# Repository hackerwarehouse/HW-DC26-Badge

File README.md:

# HW-DC26-Badge
This is the project page for the Hacker Warehouse electronic badge that was made for DEF CON 26.

## Badge Hardware Specs
* ESP32
* Atmel 32u4
* 96×64 Graphic Full Color OLED Display
* 14x Mini NeoPixel RGB LEDs
* 4 tactile buttons
* 8 Mb Storage
* 2x2 "[Shitty Add-on](https://hackaday.io/project/52950-defcon-26-shitty-add-ons "Shitty Add-on")" support
* Powered via 2 AA batteries or USB

## Badge Functions
* HID Arsenal
	* Ducky script compatible payloads (Windows and Linux demo payloads included)
	* Expanded ducky commands to support mouse movement and clicks
	* Static strings (yubico like)
	* Mouse jiggler (anti screensaver)
	* Time-based One-Time Password and HMAC-based One-Time Password (Google Authenticator mode /w keyboard insertion on demand)
* WiFi Tools
	* 802.11 channel activity monitor
	* Access point scanner / Open AP detector
	* Packet Monitor and Deauth sniffer
	* Can act as a client or access point
	* Webserver (edit filesystem files, trigger payloads remotely)
	* NTP client
* LED patterns and OLED graphics
* Misc. extras

## Usage Instructions
### Power Switch
In order to turn on the device, it must be powered via 2 AA batteries or USB. The main power switch is between the eyes.

### Buttons / UI

Up and Down is on the left side of the OLED, and Left and Right is on the right side of the OLED. From left most to right:  Down / Up / Left / Right

In order to go into a menu or run a program, click the right button. To exit most applications, click the left button. Some programs like the snake game require all 4 buttons so there is no way to clean exit, a power cycle is needed. 

### Keyboard and Mouse Payloads
When the badge is connected to a computer through the USB port, it can act as a HID device. The most common uses of that device class is keyboards and mice. Through use of the Ducky language and expanding on it to support mouse movement, the badge can trigger these scripts on demand. 

#### Via Hardware Menu
Navigate to the HID Arsenal menu, then select either the Windows or Linux Payloads menu option, depending on your target device. In the next submenu, there are five slots for payloads and pressing the right button triggers them. The slots are configurable via win.json and lin.json which defines the payload name and file location.

#### Via Webserver
Assuming the Webserver is running (via Server Tools -> Webserver Start), navigate to 10.0.5.1. Authenticate via the credentials on the OLED. You can remotely trigger the stored payloads or write on demand payloads via this interface. The stored payloads read the same win.json and lin.json files. 

### Static Strings
This mode is something like the yubico device. It is simply a static string that you can utilize with another password. This is a method of two factor authentication as the static string would be likely long and complex. Disclaimer: There is no security mechanism in place if someone were to obtain the hardware and this isn't a FIPS certified device.

### Mouse Jiggler
This mode is utilized if you have a device that you don't want the screen saver to be triggered. The mouse will move every few seconds in a defined pattern. This is useful if you have a device that forces a screensaver or device lock after x idle time. 

### Google Authenticator
This mode requires the badge to be connected to an access point that has internet connectivity so it can reach a time server as there is no RTC on the device itself. In the WiFi client tools menu, connect to an AP and make sure NTP is running. From there, in the HID Arsenal menu select the 'Google Auth (TOTP)' submenu. The six digit time based unique code will refresh every seconds. Press the right button to insert that set of digits automatically assuming the badge is connected through USB. 

### Webserver
Navigate to WiFi Server Tools -> Webserver Start. You can access the webserver if running an AP or if connected. The pages are protected through basic authentication, username and password generated dynamically and is provided on the screen.

### Blinky
There are 40+ LED patterns included. We've included our favorites set in a 5 second rotation. You can also trigger each type of pattern individually. 

### Other Modes
There are no hidden modes, but there are a few areas we didn't cover in this set of docs. Explore. 

## Configuration / Customization
### Settings menu in OLED UI
After feedback from last year on brightness settings, there are individual settings for OLED and LED brightness. Region setting is related to WiFi channel scanning.

### JSON configuration files
There are 4 different json files in SPIFFS. There are a couple ways to edit these files and get them loaded on the badge, but the easiest is through the webserver.
1. config.json = Main device configuration. Includes parameters such as LED and OLED brightness settings, ssid/password if connecting to a wireless client network, region information, and google auth HMAC. 
2. lin.json / win.json = Configuration files for the Linux and Windows KB/M payloads. 
3. static.json = Configuration file for the stored static strings. 

### Google Authenticator
If you do not have a 2 factor code from Google already, follow these steps to set obtain one and change your security settings: 
https://myaccount.google.com/security -> Signing into Google -> 2 Factor Authentication -> Authenticator App -> iphone -> click the 'Can't scan it' button and you will get a string of text that looks like this (and remember that your code will be different than this example):

Take that text, remove all the spaces, change the letter casing to all upper case, then 
input the text into config.json

## Compiling Instructions
These instructions will get you a copy of the project up and running on your local machine.
### Prerequisites
What things you need to install the software and how to install them
```
1. Arduino / compiler
2. SparkFun Pro Micro v3 com driver
https://learn.sparkfun.com/tutorials/pro-micro--fio-v3-hookup-guide/installing-windows
https://learn.sparkfun.com/tutorials/pro-micro--fio-v3-hookup-guide/installing-mac--linux
3. Libraries
  https://raw.githubusercontent.com/sparkfun/Arduino_Boards/master/IDE_Board_Manager/package_sparkfun_index.json
  https://github.com/adafruit/Adafruit_NeoPixel
  https://github.com/adafruit/Adafruit-GFX-Library
  https://github.com/adafruit/Adafruit_CircuitPlayground
  https://github.com/kitesurfer1404/WS2812FX
  https://github.com/me-no-dev/ESPAsyncWebServer
  https://github.com/me-no-dev/AsyncTCP
  https://github.com/bblanchon/ArduinoJson
  https://github.com/me-no-dev/arduino-esp32fs-plugin
  Manually copy the SSD_13XX and qMenuSystem folders to Arduino libraries folder. We included a snapshot of the other libraries used in case newer versions break our code.
4. 3.3v FTDI serial cable
5. and of course a Hacker Warehouse DC26 Badge
```
### Compiling / Flashing Atmel Code
* Set the board to SparkFun Pro Micro
* Set the processor as ATmega32u4 3.3v and NOT the 5v one

### Compiling / Flashing ESP Code
* Set the board to SparkFun ESP32 Thing

#### Programming through FTDI port
1. Flash the atmel with the 'atmel-esp32ftdi-pin7' code first, as this toggle pin 7 and the rx/tx switch to change the serial port communiction to the FTDI port
2. Connect FTDI cable to the board while holding the left button down (which is on the right side, top button)
3. Upload code. Speed setting doesn't really matter, we've been using 921600.
4. To put the atmel back to its original state, program 'atmel-km-relay' the code to it.

#### Programming through USB port / Atmel
Pass through programming doesn't work at the time of writing. Communication is passed through, but something is holding up the ESP32 from fully going into the programming mode

### Uploading SPIFFS files
The keyboard/mouse payloads, configuration files, webserver files are all files that are loaded into a special section in storage marked as SPIFFS. While still having pin 7 set to allow for the FTDI connection, use the 'ESP32 Sketch Data Upload' function in the tools menu. This will compress and compile all the files in the 'data' folder, and upload it. 

## Expanding on your own
### Adding to menu
* See files HW-DC26-Badge.ino and mainmenu.h
* Look at the main switch statement in the .ino file
* Look any of the mainmenu.h examples for how it corresponds to the display

### Button mapping / Escape code
* See files HW-DC26-Badge.ino and blinky.cpp 
* Button mapping is in the beginning of the .ino file
* Look at the LED_Flashlight function for an example of button usage and how to quit the loop and go back to main menu

## Background / timeline of badge development
* Second custom hardware / electronics project trying to improve upon the things we learned from last year
	* Changed from the ESP8266 to the newer ESP32 so we could leverage prior code and focus on enhancements 
	* Added an LDO regulator so badge or connected computer doesn't freak out on voltage
* 3 hardware revisions = 2 prototype runs = 4-5 months
	* The hardware revisions this year were minor in comparison to last year. It was mainly due to the 2x2 Shitty Add-on and orientation of the connector
	* Tried to start earlier (lesson learned last year) but scheduling conflicts put us back to essentially the same timeline as last year
* 5 week code sprint before code needing to be frozen for mass badge flashing
	* This was a massive improvement from last year from a time / rush perspective
	* Still wanted to add more into it such as BLE, but ram out of storage and ram. 

## Authors / Contributors
* **Garrett Gee**

## Acknowledgments
* Hat tip to anyone who's code was used, looked at, referenced, etc
* All the supporters of this project

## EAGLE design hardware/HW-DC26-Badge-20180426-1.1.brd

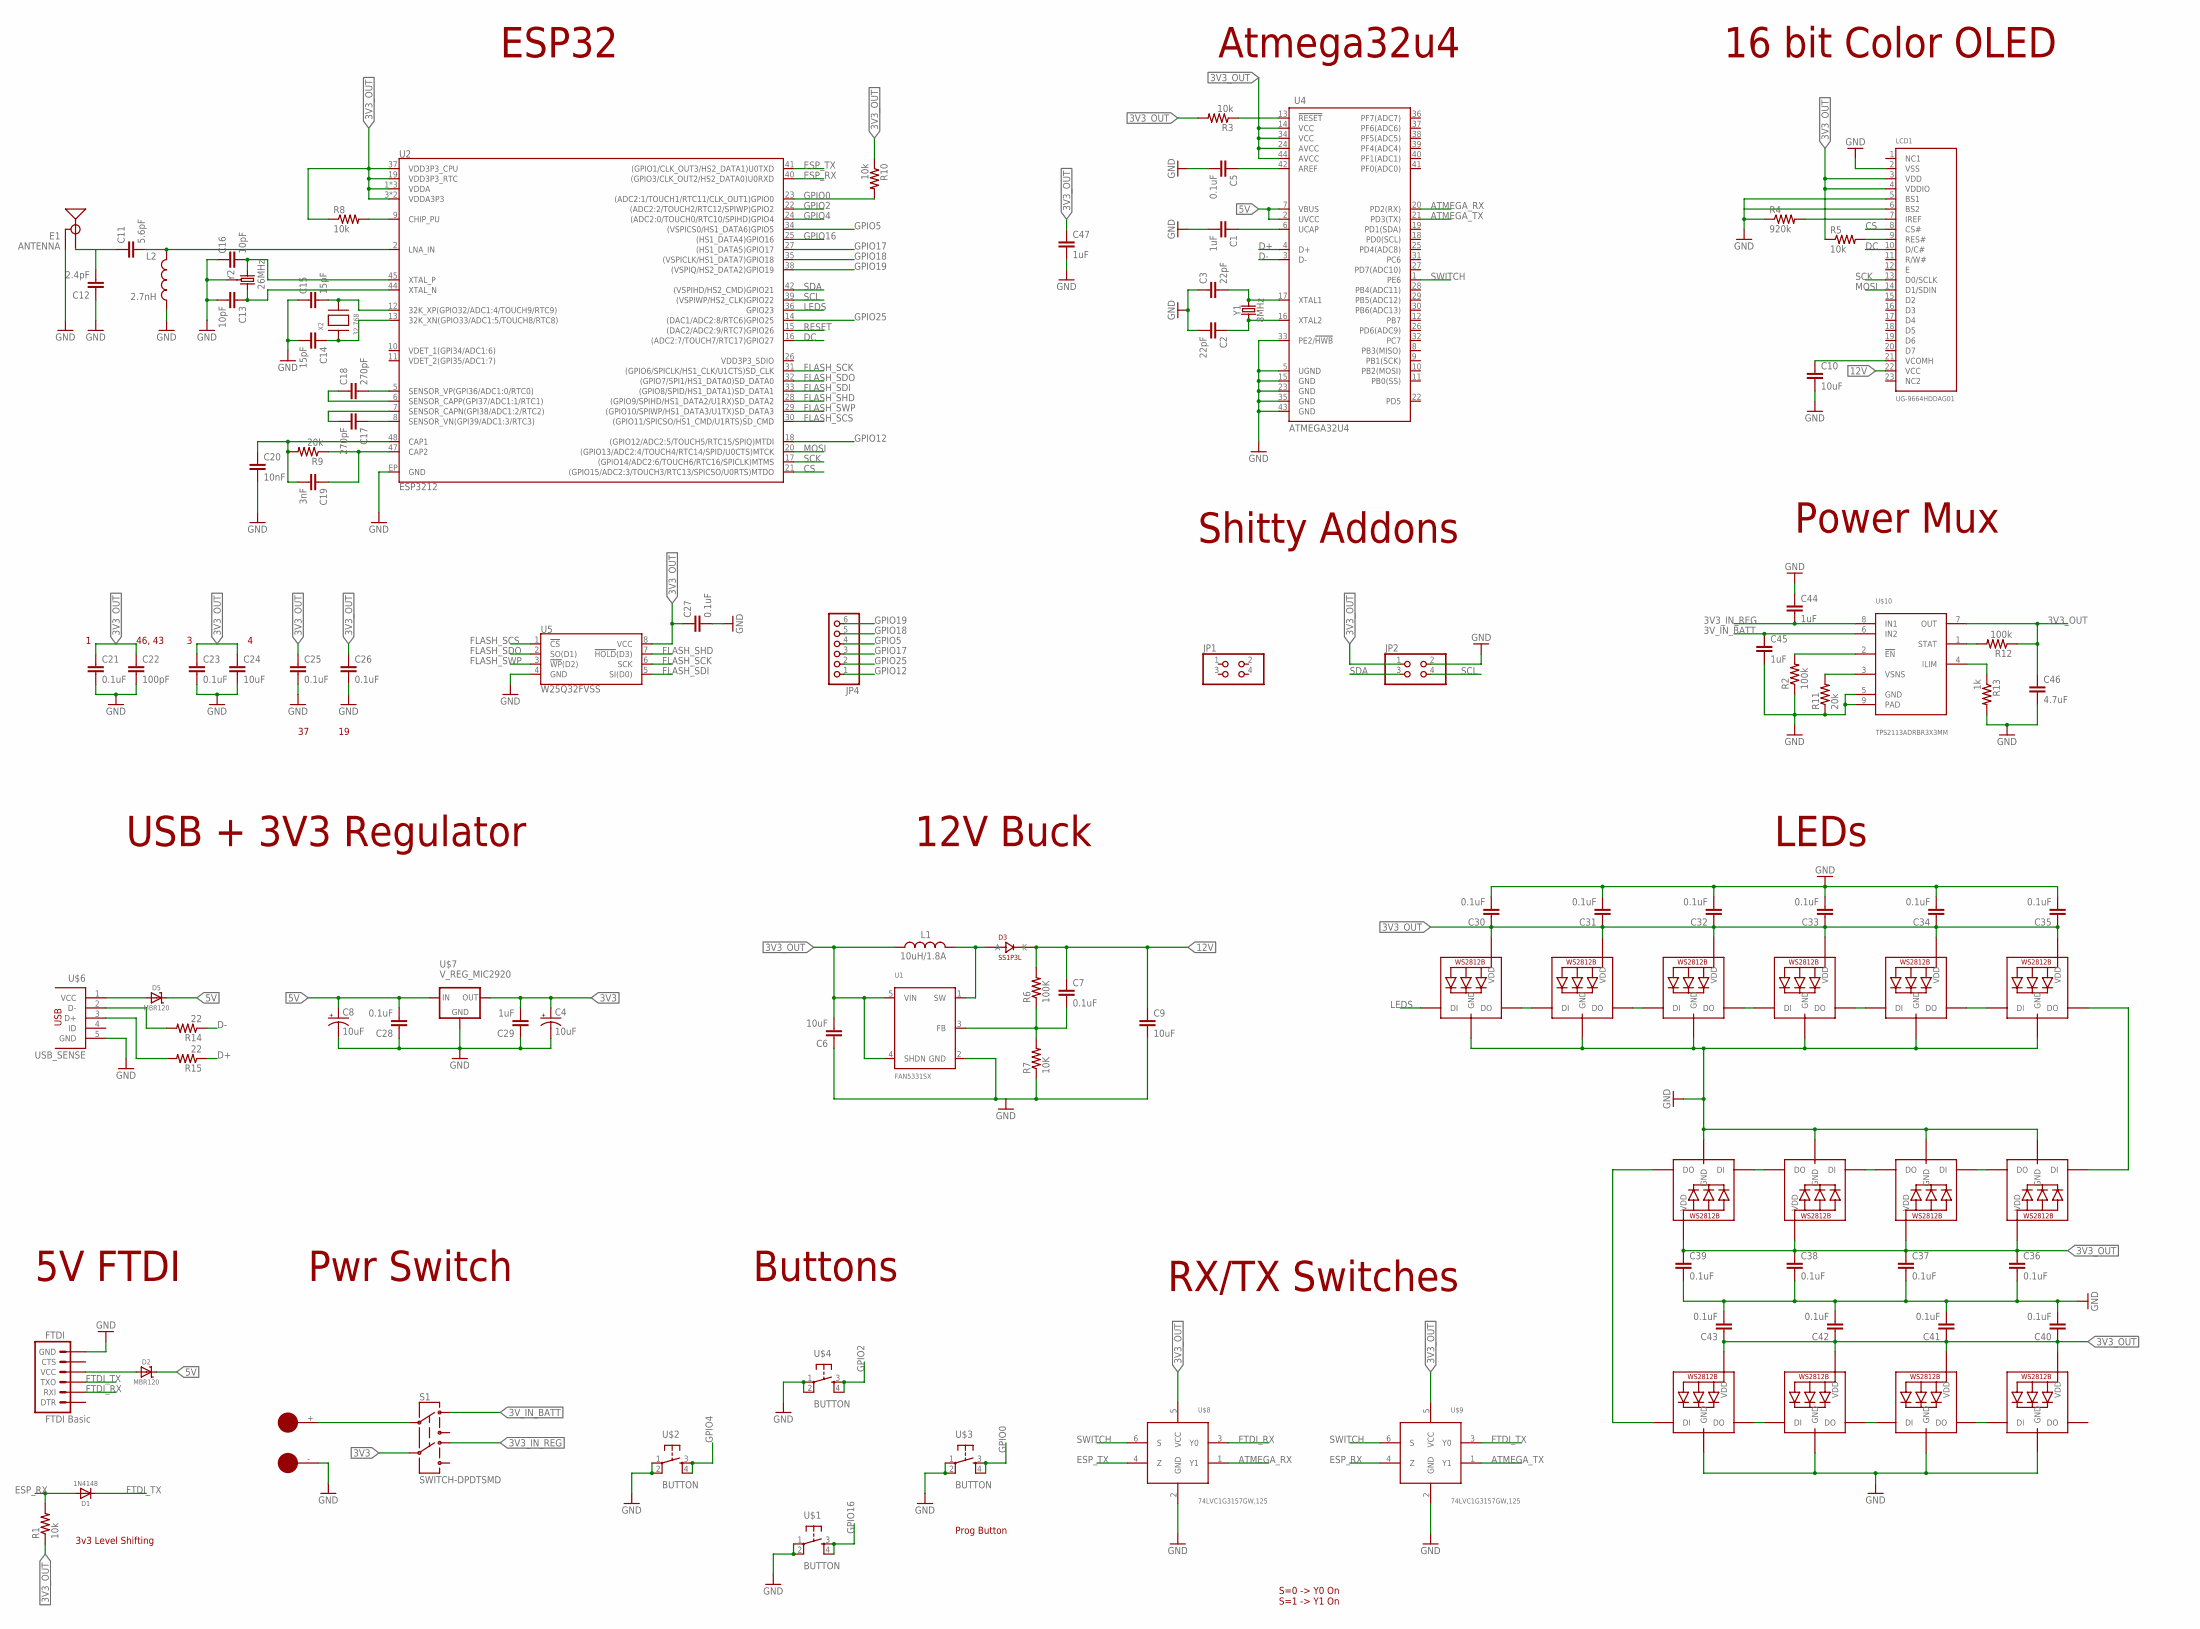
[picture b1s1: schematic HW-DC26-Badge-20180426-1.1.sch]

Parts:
C1, C29, C44, C45, C47: 1uF; CAP0603
C2, C3: 22pF; CAP0603
C4, C8: 10uF; EIA3216
C5, C7, C21, C23, C25, C26, C27, C28, C30, C31, C32, C33, C34, C35, C36, C37, C38, C39, C40, C41, C42, C43: 0.1uF; CAP0603
C6, C9, C10, C24: 10uF; CAP0603
C11: 5.6pF; CAP0603
C12: 2.4pF; CAP0603
C13, C16: 10pF; CAP0603
C14, C15: 15pF; CAP0603
C17, C18: 270pF; CAP0603
C19: 3nF; CAP0603
C20: 10nF; CAP0603
C22: 100pF; CAP0603
C46: 4.7uF; CAP0603
D1: 1N4148; SOD-323
D2, D5: MBR120; SOD-123
D3: SS1P3L; DO220AAL
E1: ANTENNA; TRACE_ANTENNA_2.4GHZ_25.7MM_TUNED
FTDI: FTDI Basic; 1X06
JP1, JP2: PINHD-2X2; 2X02
JP4: PINHD-1X6; 1X06
L1: 10uH/1.8A; SRU5028
L2: 2.7nH; 0603
LCD1: UG-9664HDDAG01; UG-9664HDDAG01_WRAPAROUND
LED1, LED2, LED3, LED4, LED5, LED6, LED7, LED8, LED9, LED10, LED11, LED12, LED13, LED14: WS2812B3535; LED3535
R1, R3, R5, R8, R10: 10k; RES-0603
R2, R12: 100k; RES-0603
R4: 920k; RES-0603
R6: 100K; RES-0603
R7: 10K; RES-0603
R9, R11: 20k; RES-0603
R13: 1k; RES-0603
R14, R15: 22; RES-0603
S1: SWITCH-DPDTSMD; AYZ0202
U1: FAN5331SX; SOT23-5
U2: ESP3212; QFN48-0.4MM
U4: ATMEGA32U4; QFN-44-NOPAD_1:1-OUTFAKES
U5: W25Q32FVSS; SOIC-8
U$1, U$2, U$3, U$4: BUTTON
U$5: BAT_HOLD; AA
U$6: USB_SENSE; USB-MICRO-TH-SUPPORT
U$7: V_REG_MIC2920; SOT223
U$8, U$9: 74LVC1G3157GW,125; SOT-363
U$10: TPS2113ADRBR3X3MM; 8-VDFN
X2: 32.768; XTAL3215
Y1: 8MHz; CRYSTAL-SMD-5X3.2-4PAD
Y2: 26MHz; CRYSTAL-SMD-3.2X2.5

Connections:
3V3: C4.A (+), C29.2, S1.5, U$7.3 (OUT)
3V3_IN_REG: C44.2, S1.4, U$10.8 (IN1)
3V3_OUT: C6.2, C21.1, C22.1, C23.1, C24.1, C25.1, C26.1, C27.1, C30.1, C31.1, C32.1, C33.1, C34.1, C35.1, C36.1, C37.1, C38.1, C39.1, C40.1, C41.1, C42.1, C43.1, C46.1, C47.1, JP2.1, L1.1, LCD1.3 (VDD), LCD1.4 (VDDIO), LED1.2 (VDD), LED2.2 (VDD), LED3.2 (VDD), LED4.2 (VDD), LED5.2 (VDD), LED6.2 (VDD), LED7.2 (VDD), LED8.2 (VDD), LED9.2 (VDD), LED10.2 (VDD), LED11.2 (VDD), LED12.2 (VDD), LED13.2 (VDD), LED14.2 (VDD), R1.1, R3.2, R5.1, R8.1, R10.1, R12.1, U1.4 (SHDN), U1.5 (VIN), U2.1 (VDDA), U2.3 (VDDA3P3), U2.4 (VDDA3P3), U2.19 (VDD3P3_RTC), U2.37 (VDD3P3_CPU), U2.43 (VDDA), U2.46 (VDDA), U4.14 (VCC), U4.24 (AVCC), U4.34 (VCC), U4.44 (AVCC), U5.8 (VCC), U$8.5 (VCC), U$9.5 (VCC), U$10.7 (OUT)
3V_IN_BATT: C45.1, S1.1, U$10.6 (IN2)
5V: C8.A (+), C28.2, D2.C, D5.C, U4.2 (UVCC), U4.7 (VBUS), U$7.1 (IN)
12V: C7.1, C9.1, D3.P$1 (K), LCD1.22 (VCC), R6.2
ATMEGA_RX: U4.20 (PD2(RX)), U$8.1 (Y1)
ATMEGA_TX: U4.21 (PD3(TX)), U$9.1 (Y1)
CS: LCD1.8 (CS#), U2.21 ((GPIO15/ADC2:3/TOUCH3/RTC13/SPICSO/U0RT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)
D+: R15.1, U4.4 (D+)
D-: R14.1, U4.3 (D-)
DC: LCD1.10 (D/C#), U2.16 ((ADC2:7/TOUCH7/RTC17)GPIO27)
ESP_RX: D1.A, R1.2, U2.40 ((GPIO3/CLK_OUT2/HS2_DATA0)U0RXD), U$9.4 (Z)
ESP_TX: U2.41 ((GPIO1/CLK_OUT3/HS2_DATA1)U0TXD), U$8.4 (Z)
FLASH_SCK: U2.31 ((GPIO6/SPICLK/HS1_CLK/U1CTS)SD_CLK), U5.6 (SCK)
FLASH_SCS: U2.30 ((GPIO11/SPICSO/HS1_CMD/U1RTS)SD_CMD), U5.1 (!CS!)
FLASH_SDI: U2.33 ((GPIO8/SPID/HS1_DATA1)SD_DATA1), U5.5 (SI(D0))
FLASH_SDO: U2.32 ((GPIO7/SPI1/HS1_DATA0)SD_DATA0), U5.2 (SO(D1))
FLASH_SHD: U2.28 ((GPIO9/SPIHD/HS1_DATA2/U1RX)SD_DATA2), U5.7 (!HOLD!(D3))
FLASH_SWP: U2.29 ((GPIO10/SPIWP/HS1_DATA3/U1TX)SD_DATA3), U5.3 (!WP!(D2))
FTDI_RX: FTDI.2 (RXI), U$8.3 (Y0)
FTDI_TX: D1.C, FTDI.3 (TXO), U$9.3 (Y0)
GND: C1.2, C2.2, C3.1, C4.C (-), C5.2, C6.1, C8.C (-), C9.2, C10.2, C12.1, C13.2, C14.2, C15.1, C16.1, C20.2, C21.2, C22.2, C23.2, C24.2, C25.2, C26.2, C27.2, C28.1, C29.1, C30.2, C31.2, C32.2, C33.2, C34.2, C35.2, C36.2, C37.2, C38.2, C39.2, C40.2, C41.2, C42.2, C43.2, C44.1, C45.2, C46.2, C47.2, E1.GND, E1.GND2 (GND), FTDI.6 (GND), JP2.2, L2.2, LCD1.2 (VSS), LCD1.5 (BS1), LED1.4 (GND), LED2.4 (GND), LED3.4 (GND), LED4.4 (GND), LED5.4 (GND), LED6.4 (GND), LED7.4 (GND), LED8.4 (GND), LED9.4 (GND), LED10.4 (GND), LED11.4 (GND), LED12.4 (GND), LED13.4 (GND), LED14.4 (GND), R2.1, R4.1, R7.1, R11.1, R13.2, U1.2 (GND), U2.EP (GND), U4.5 (UGND), U4.15 (GND), U4.23 (GND), U4.33 (PE2/!HWB), U4.35 (GND), U4.43 (GND), U5.4 (GND), U$1.1, U$1.2, U$2.1, U$2.2, U$3.1, U$3.2, U$4.1, U$4.2, U$5.-, U$6.5 (GND), U$7.2 (GND), U$7.4 (GND), U$8.2 (GND), U$9.2 (GND), U$10.5 (GND), U$10.9 (PAD), Y2.2 (GND), Y2.4 (GND)
GPIO0: R10.2, U2.23 ((ADC2:1/TOUCH1/RTC11/CLK_OUT1)GPIO0), U$3.3, U$3.4
GPIO2: U2.22 ((ADC2:2/TOUCH2/RTC12/SPIWP)GPIO2), U$4.3, U$4.4
GPIO4: U2.24 ((ADC2:0/TOUCH0/RTC10/SPIHD)GPIO4), U$2.3, U$2.4
GPIO5: JP4.4, U2.34 ((VSPICS0/HS1_DATA6)GPIO5)
GPIO12: JP4.1, U2.18 ((GPIO12/ADC2:5/TOUCH5/RTC15/SPIQ)MTDI)
GPIO16: U2.25 ((HS1_DATA4)GPIO16), U$1.3, U$1.4
GPIO17: JP4.3, U2.27 ((HS1_DATA5)GPIO17)
GPIO18: JP4.5, U2.35 ((VSPICLK/HS1_DATA7)GPIO18)
GPIO19: JP4.6, U2.38 ((VSPIQ/HS2_DATA2)GPIO19)
GPIO25: JP4.2, U2.14 ((DAC1/ADC2:8/RTC6)GPIO25)
LEDS: LED5.1 (DI), U2.36 (GPIO23)
MOSI: LCD1.14 (D1/SDIN), U2.20 ((GPIO13/ADC2:4/TOUCH4/RTC14/SPID/U0CTS)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)
unnamed: C3.2, U4.17 (XTAL1), Y1.3 (2)
unnamed: R3.1, U4.13 (!RESET)
unnamed: C1.1, U4.6 (UCAP)
unnamed: C5.1, U4.42 (AREF)
unnamed: R14.2, U$6.2 (D-)
unnamed: C10.1, LCD1.21 (VCOMH)
unnamed: D3.P$2 (A), L1.2, U1.1 (SW)
unnamed: C2.1, U4.16 (XTAL2), Y1.1
unnamed: LED1.1 (DI), LED14.3 (DO)
unnamed: C7.2, R6.1, R7.2, U1.3 (FB)
unnamed: LCD1.7 (IREF), R4.2
unnamed: S1.2, U$5.+
unnamed: R8.2, U2.9 (CHIP_PU)
unnamed: C16.2, U2.45 (XTAL_P), Y2.1
unnamed: C11.1, C12.2, E1.ANT (SIGNAL)
unnamed: LED1.3 (DO), LED2.1 (DI)
unnamed: D2.A, FTDI.4 (VCC)
unnamed: LED5.3 (DO), LED6.1 (DI)
unnamed: C19.2, C20.1, R9.2, U2.48 (CAP1)
unnamed: C11.2, L2.1, U2.2 (LNA_IN)
unnamed: C13.1, U2.44 (XTAL_N), Y2.3 (2)
unnamed: C19.1, R9.1, U2.47 (CAP2)
unnamed: C15.2, U2.12 (32K_XP(GPIO32/ADC1:4/TOUCH9/RTC9)), X2.P$2
unnamed: C14.1, U2.13 (32K_XN(GPIO33/ADC1:5/TOUCH8/RTC8)), X2.P$1
unnamed: C18.2, U2.5 (SENSOR_VP(GPI36/ADC1:0/RTC0))
unnamed: C18.1, U2.6 (SENSOR_CAPP(GPI37/ADC1:1/RTC1))
unnamed: C17.2, U2.7 (SENSOR_CAPN(GPI38/ADC1:2/RTC2))
unnamed: C17.1, U2.8 (SENSOR_VN(GPI39/ADC1:3/RTC3))
unnamed: D5.A, U$6.1 (VCC)
unnamed: LED6.3 (DO), LED7.1 (DI)
unnamed: LED7.3 (DO), LED8.1 (DI)
unnamed: LED8.3 (DO), LED9.1 (DI)
unnamed: LED9.3 (DO), LED11.1 (DI)
unnamed: LED11.3 (DO), LED13.1 (DI)
unnamed: LED10.1 (DI), LED13.3 (DO)
unnamed: LED10.3 (DO), LED12.1 (DI)
unnamed: LED12.3 (DO), LED14.1 (DI)
unnamed: LED2.3 (DO), LED3.1 (DI)
unnamed: LED3.3 (DO), LED4.1 (DI)
unnamed: R15.2, U$6.3 (D+)
unnamed: R2.2, U$10.2 (!EN)
unnamed: R11.2, U$10.3 (VSNS)
unnamed: R12.2, U$10.1 (STAT)
unnamed: R13.1, U$10.4 (ILIM)
RESET: LCD1.9 (RES#), R5.2, U2.15 ((DAC2/ADC2:9/RTC7)GPIO26)
SCK: LCD1.13 (D0/SCLK), U2.17 ((GPIO14/ADC2:6/TOUCH6/RTC16/SPICLK)MTMS)
SCL: JP2.4, U2.39 ((VSPIWP/HS2_CLK)GPIO22)
SDA: JP2.3, U2.42 ((VSPIHD/HS2_CMD)GPIO21)
SWITCH: U4.1 (PE6), U$8.6 (S), U$9.6 (S)

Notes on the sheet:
ESP32
Atmega32u4
16 bit Color OLED
USB + 3V3 Regulator
5V FTDI
12V Buck
Pwr Switch
Buttons
Shitty Addons
LEDs
S=0 -> Y0 On S=1 -> Y1 On
RX/TX Switches
46, 43
Power Mux
3v3 Level Shifting
Prog Button

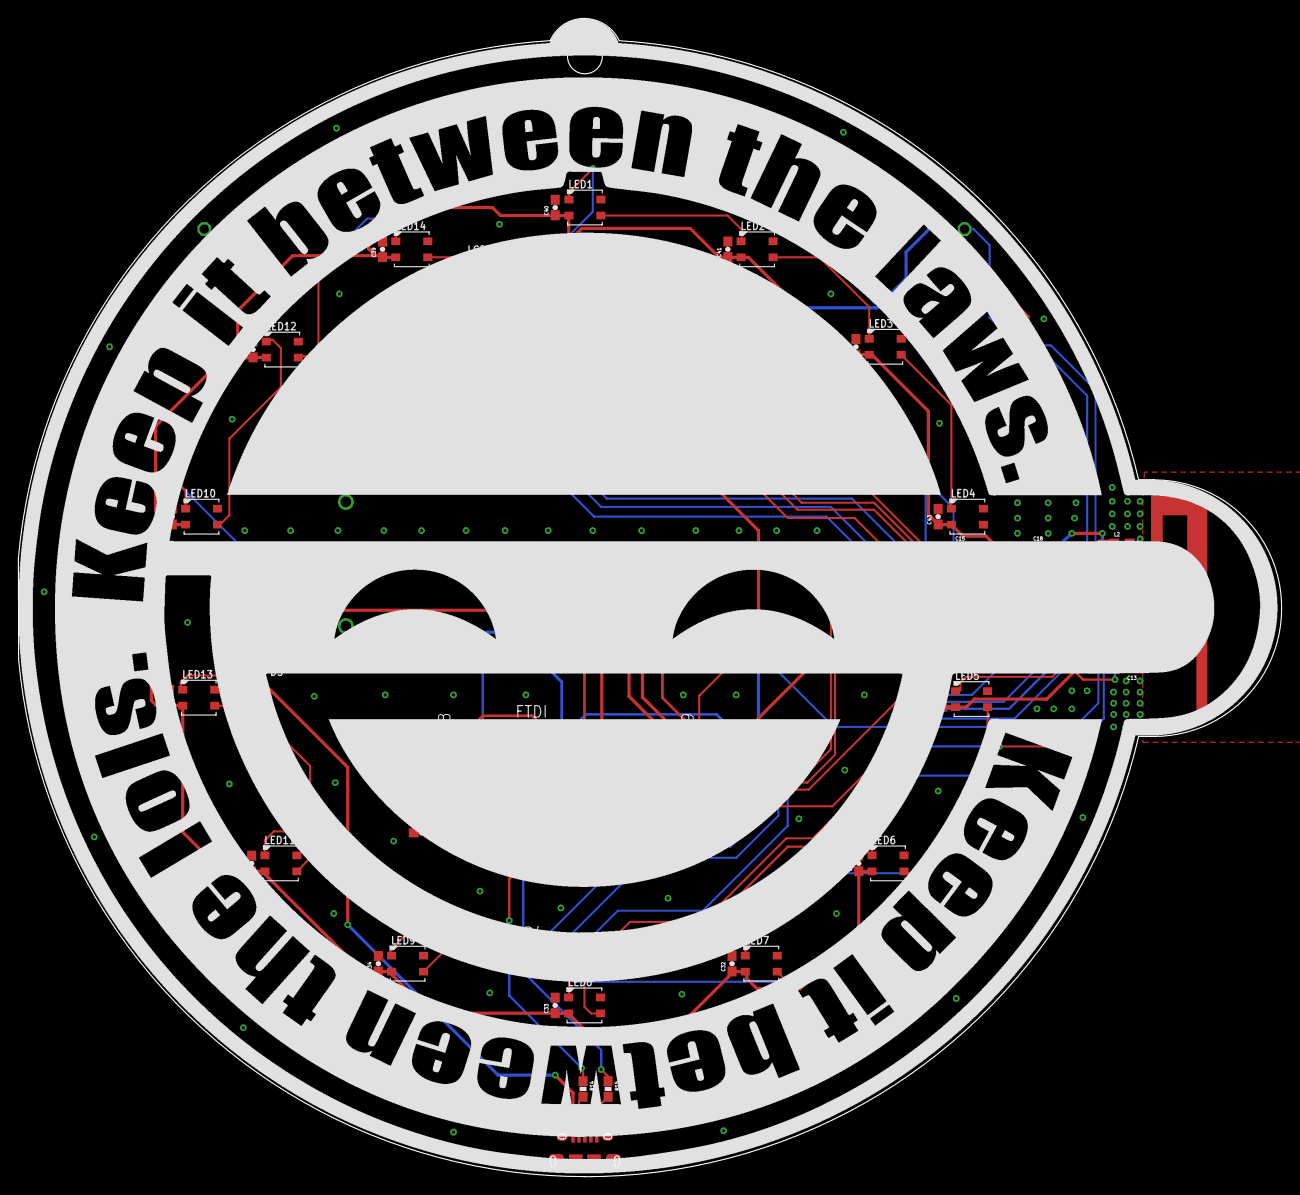
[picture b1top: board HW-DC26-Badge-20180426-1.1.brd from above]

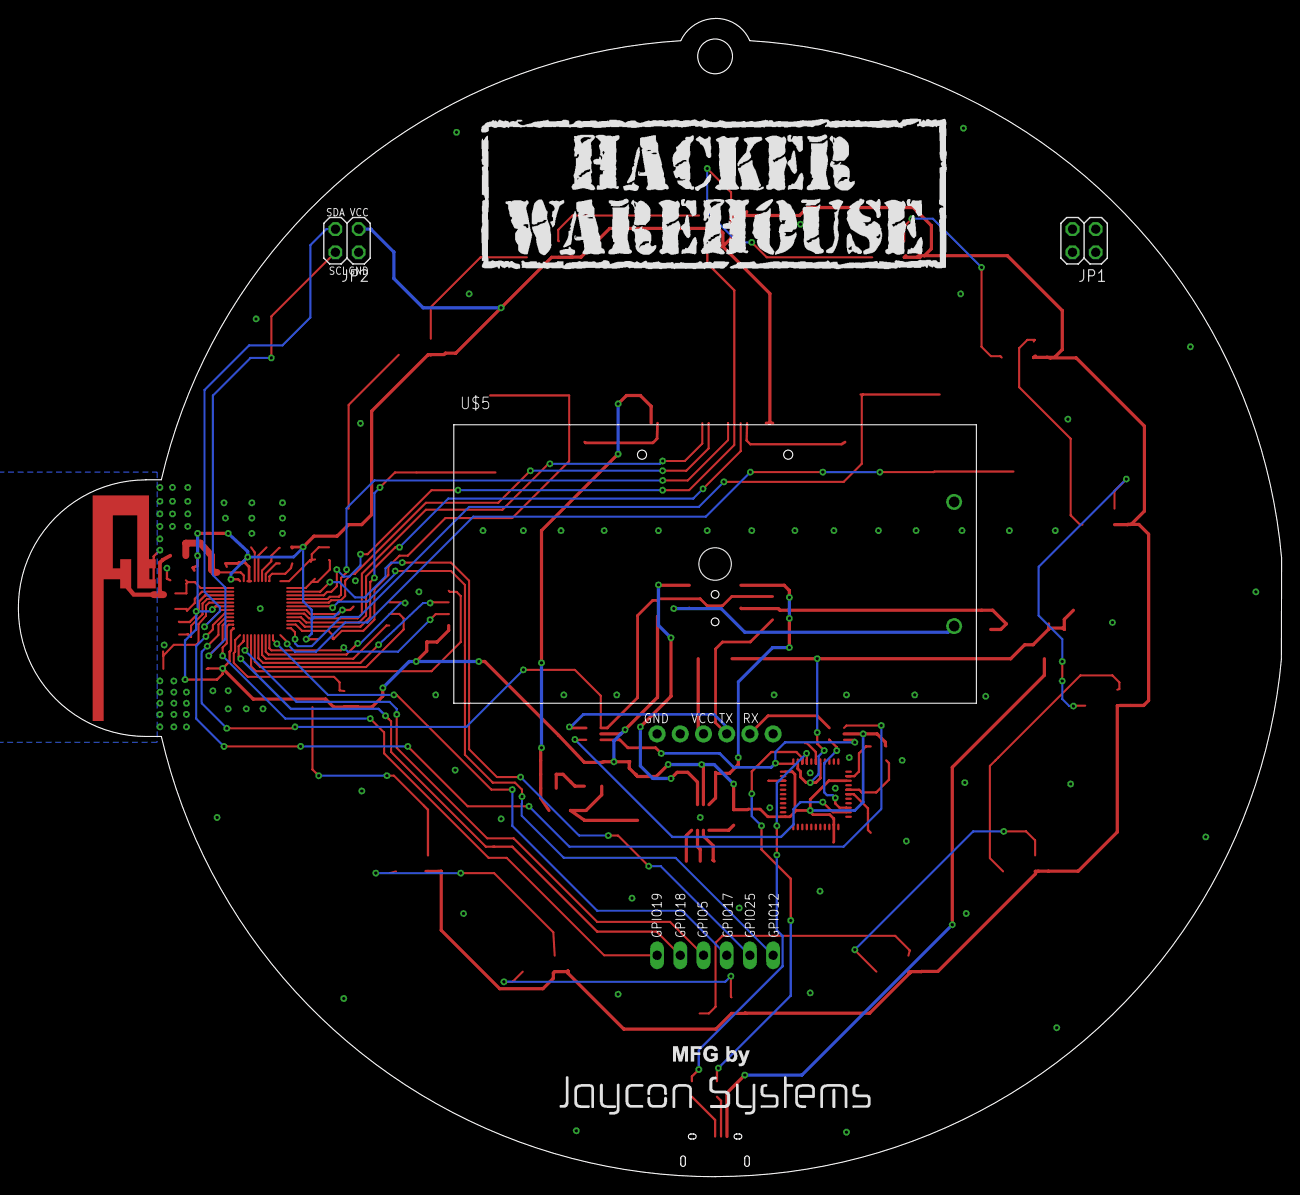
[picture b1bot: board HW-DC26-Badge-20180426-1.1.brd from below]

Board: 2 copper layers, 138.3 x 126.8 mm, 106 parts (3 on the bottom side), 84 nets.

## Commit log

2018-06-07 Snapshot from 2018-06-03
2018-06-08 Docs update
2018-09-16 final board design
2018-09-16 note about power switch

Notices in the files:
parts and their libraries:
SparkFun-DigitalIC: Licensing: CC v3.0 Share-Alike You are welcome to use this library for commercial purposes.
Jaycon OPL Capacitors: Licensing: Creative Commons ShareAlike 4.0 International - https://creativecommons.org/licenses/by-sa/4.0
